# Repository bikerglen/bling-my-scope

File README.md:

# bling-my-scope

## Installing

sudo apt update

sudo apt upgrade

sudo apt install libopencv-dev python3-opencv

python3 -c "import cv2; print(cv2.__version__)"

sudo pip3 install rpi_ws281x adafruit-circuitpython-neopixel

sudo python3 -m pip install --force-reinstall adafruit-blinka

## Connecting

Connect a strip of neopixels to GPIO D18 on the Raspberry Pi.

## Configuring

Adjust the gamma variable to get the desired effect. 1.25 works well for a scope waveform window, 2.8 works well for normal video.

Set the number of pixels along each of the scope using the n???Pixels variables. Pixels start in the top left corner when facing the front of the scope and continue in a clockwise direction around the scope.

## Running

sudo python3 bling_800x600.py

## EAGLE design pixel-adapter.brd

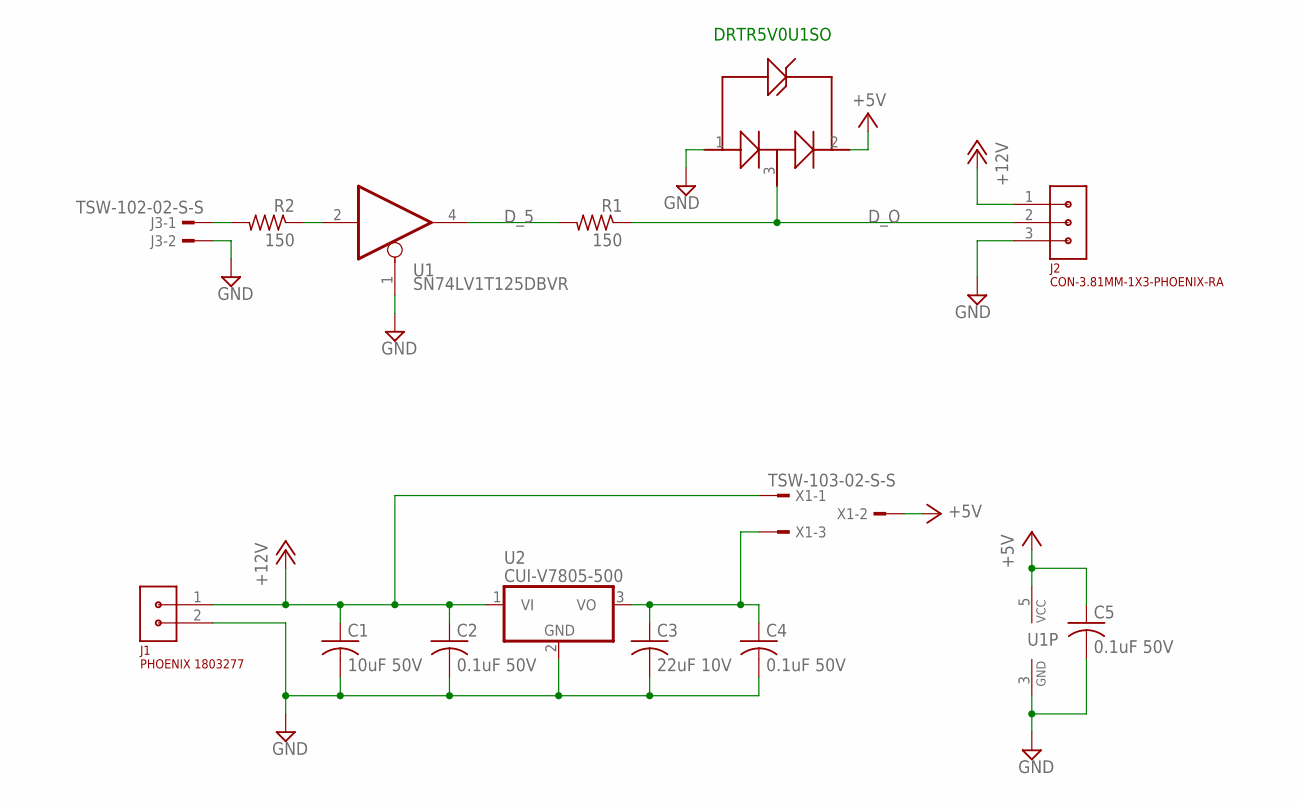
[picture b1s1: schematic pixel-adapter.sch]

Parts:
C1: 10uF 50V; C1210K; MFR_PART_NO C1210C106K5RACTU
C2, C4: 0.1uF 50V; C1206; MFR_PART_NO C1206S104M5RACTU
C3: 22uF 10V; C1206K; MFR_PART_NO C1206C226K8RAC7800
C5: 0.1uF 50V; C0603K; MFR_PART_NO C1206S104M5RACTU
D1: DRTR5V0U1SO; SOT23-3
J1: PHOENIX 1803277; CON-PHOENIX-3.81-1X2-RA
J2: CON-3.81MM-1X3-PHOENIX-RA; CON-PHOENIX-3.81-1X3-RA
J3: TSW-102-02-S-S
R1, R2: 150; M1206
U1: SN74LV1T125DBVR; SOT23-5; MFR_PART_NO SN74LV1T125DBVR
U2: CUI-V7805-500; CUI-78XX-500
X1: TSW-103-02-S-S

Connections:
+5V: C5.1, D1.2, U1.5 (VCC), X1.2
+12V: C1.1, C2.1, J1.1, J2.1, U2.1 (VI), X1.1
DIN: J3.1, R2.2
DIN_O: R2.1, U1.2 (I)
D_5: R1.2, U1.4 (O)
D_O: D1.3 (1), J2.2, R1.1
GND: C1.2, C2.2, C3.2, C4.2, C5.2, D1.1 (3), J1.2, J2.3, J3.2, U1.1 (OE), U1.3 (GND), U2.2 (GND)
VREG: C3.1, C4.1, U2.3 (VO), X1.3

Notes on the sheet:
DRTR5V0U1SO

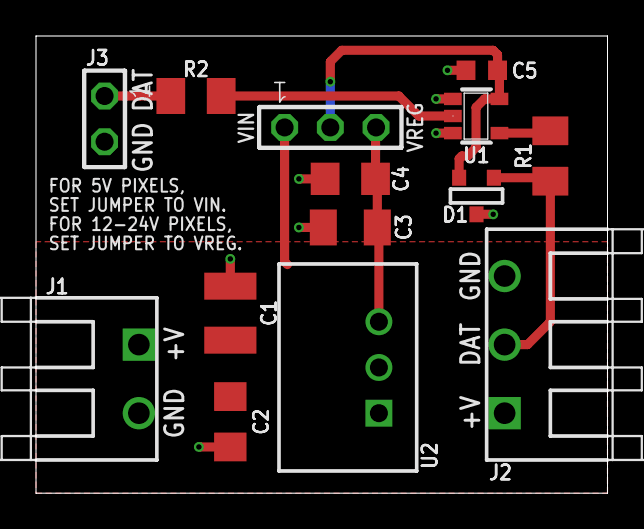
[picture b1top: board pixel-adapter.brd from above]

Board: 2 copper layers, 31.8 x 25.4 mm, 14 parts (0 on the bottom side), 8 nets.

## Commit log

2023-03-08 initial checkin of parameterized code
2023-03-08 add pixel adatper board and schematic
